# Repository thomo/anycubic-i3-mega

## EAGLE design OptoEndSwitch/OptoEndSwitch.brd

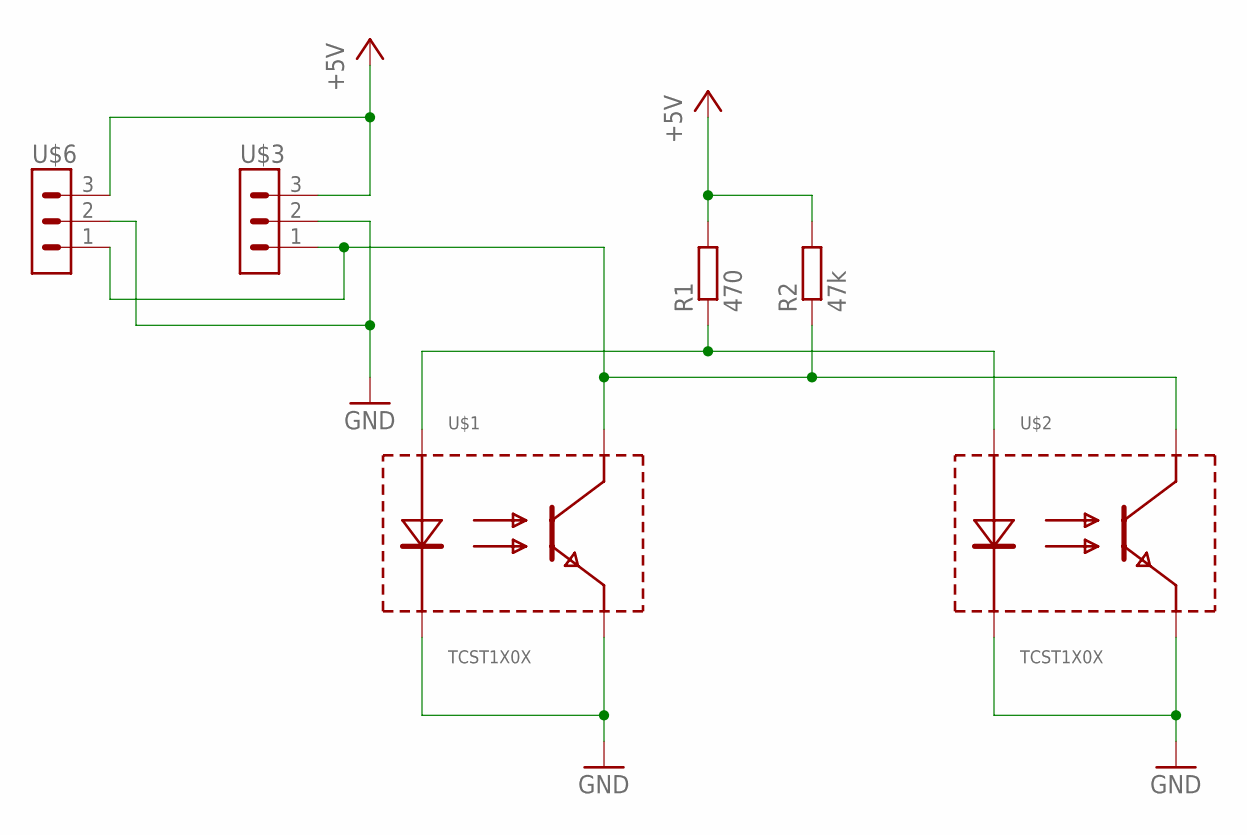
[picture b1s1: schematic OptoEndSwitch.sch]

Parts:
R1: 470; 0207/10
R2: 47k; 0207/10
U$1, U$2: TCST1X0X
U$3, U$6: JST-3PSIDE-SHORT; XH-A-1-SIDE-3P

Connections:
+5V: R1.2, R2.2, U$3.3, U$6.3
GND: U$1.D, U$1.E, U$2.D, U$2.E, U$3.2, U$6.2
unnamed: R2.1, U$1.D+, U$2.D+, U$3.1, U$6.1
unnamed: R1.1, U$1.E+, U$2.E+

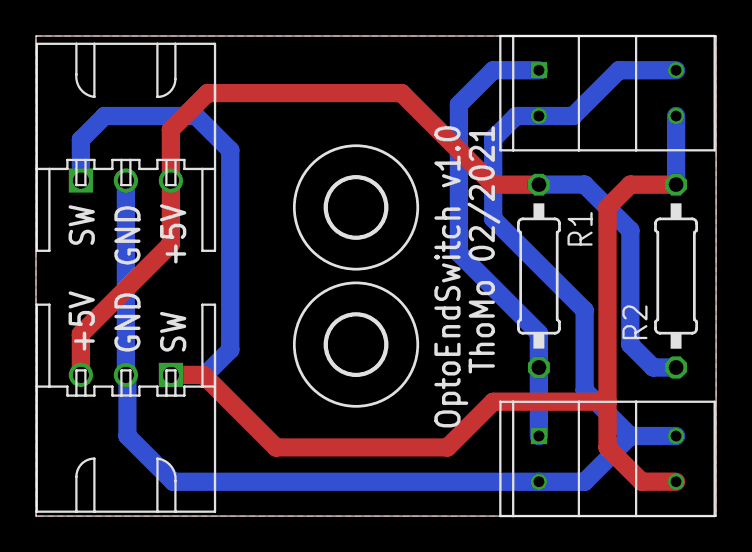
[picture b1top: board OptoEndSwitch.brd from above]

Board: 2 copper layers, 37.8 x 26.7 mm, 8 parts (0 on the bottom side), 4 nets.

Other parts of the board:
U$4, U$5: 3,2

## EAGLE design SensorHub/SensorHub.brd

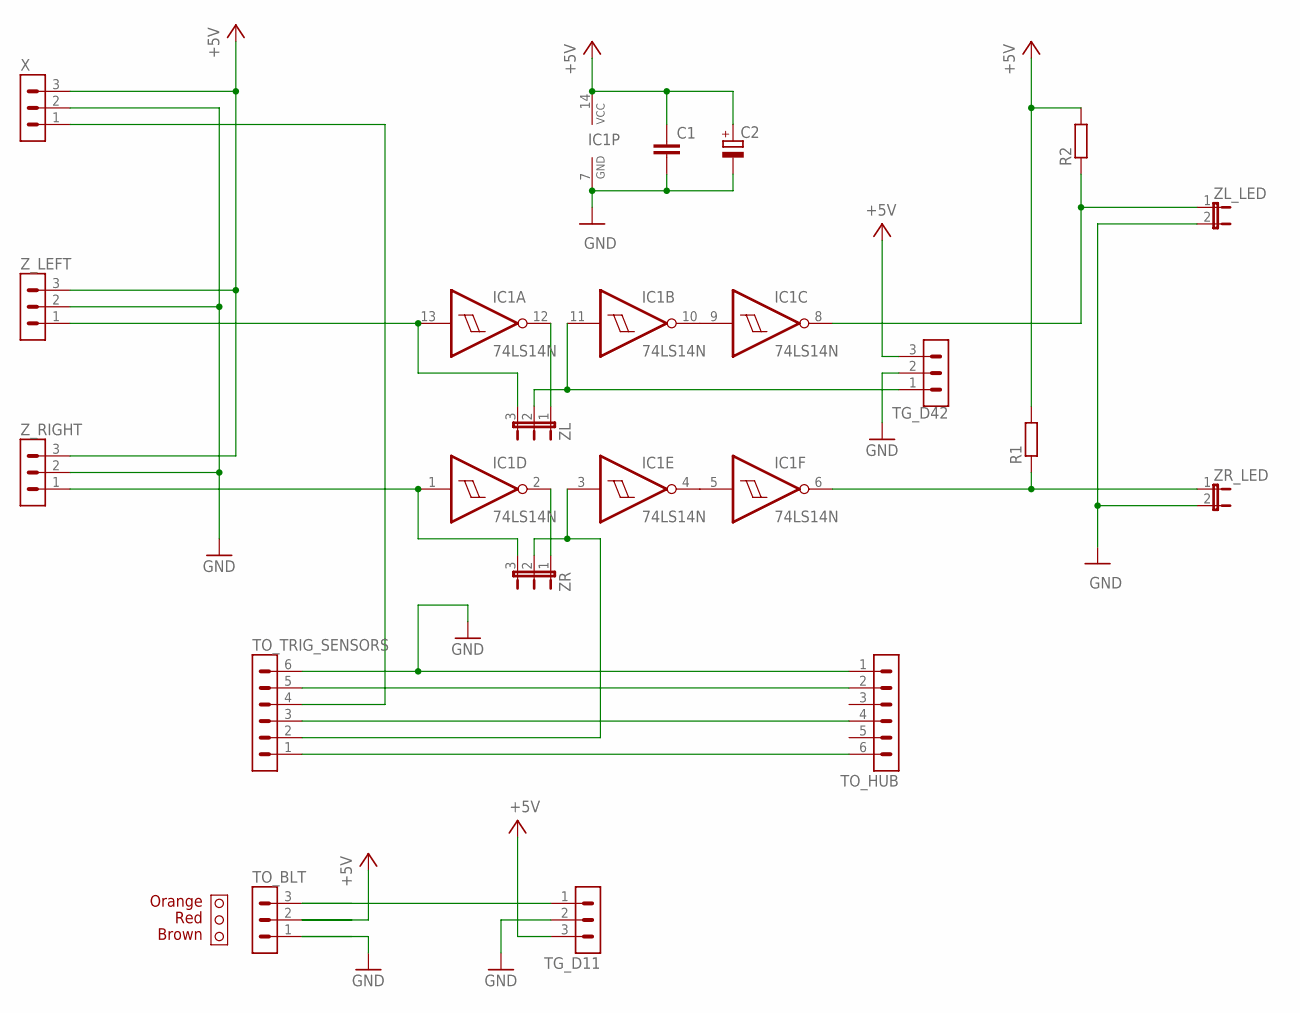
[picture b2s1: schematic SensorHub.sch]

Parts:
C1: C-EU050-030X075; C050-030X075
C2: CPOL-EUE3.5-8; E3,5-8
IC1: 74LS14N; DIL14
R1, R2: R-EU_0207/10; 0207/10
TG_D11, TG_D42: JST-3PTOP; XH-A-TOP-3P
TO_BLT: JST-3PTOP; XH-A-TOP-3P
TO_HUB: JST-6PPH-TOP; PH-TOP-6P
TO_TRIG_SENSORS: JST-6PPH-TOP; PH-TOP-6P
X: JST-3PTOP; XH-A-TOP-3P
ZL: JP2E; JP2
ZL_LED: ZL LED; JP1
ZR: JP2E; JP2
ZR_LED: ZR LED; JP1
Z_LEFT: JST-3PTOP; XH-A-TOP-3P
Z_RIGHT: JST-3PTOP; XH-A-TOP-3P

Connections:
+5V: C1.1, C2.+, IC1.14 (VCC), R1.2, R2.2, TG_D11.3, TG_D42.3, TO_BLT.2, X.3, Z_LEFT.3, Z_RIGHT.3
GND: C1.2, C2.-, IC1.7 (GND), TG_D11.2, TG_D42.2, TO_BLT.1, TO_HUB.1, TO_TRIG_SENSORS.6, X.2, ZL_LED.2, ZR_LED.2, Z_LEFT.2, Z_RIGHT.2
unnamed: IC1.6 (O), R1.1, ZR_LED.1
unnamed: IC1.13 (I), ZL.3, Z_LEFT.1
unnamed: IC1.1 (I), ZR.3, Z_RIGHT.1
unnamed: TO_HUB.4, TO_TRIG_SENSORS.3
unnamed: TO_HUB.2, TO_TRIG_SENSORS.5
unnamed: IC1.11 (I), TG_D42.1, ZL.2
unnamed: TO_HUB.6, TO_TRIG_SENSORS.1
unnamed: IC1.9 (I), IC1.10 (O)
unnamed: TO_TRIG_SENSORS.4, X.1
unnamed: IC1.4 (O), IC1.5 (I)
unnamed: IC1.12 (O), ZL.1
unnamed: TG_D11.1, TO_BLT.3
unnamed: IC1.2 (O), ZR.1
unnamed: IC1.3 (I), TO_TRIG_SENSORS.2, ZR.2
TG_D42: IC1.8 (O), R2.1, ZL_LED.1

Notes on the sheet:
Orange
Red
Brown

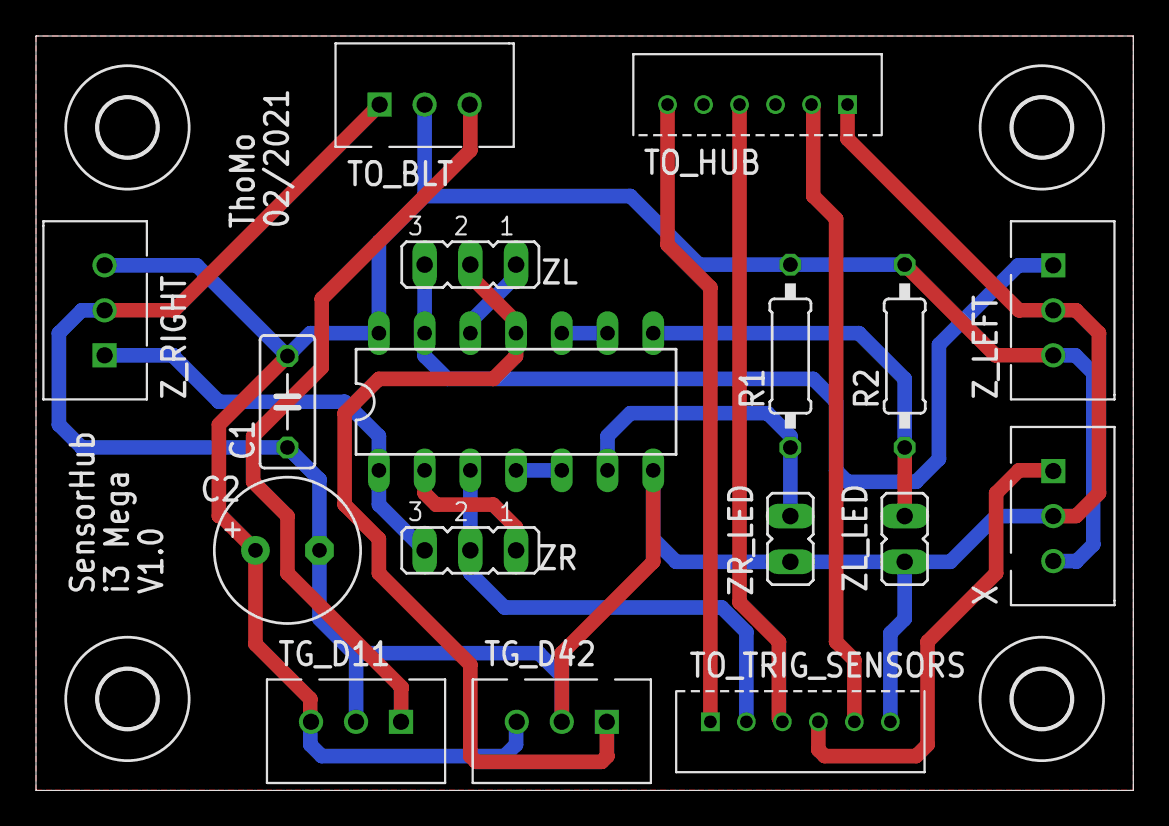
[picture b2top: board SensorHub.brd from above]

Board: 2 copper layers, 61.0 x 41.9 mm, 21 parts (0 on the bottom side), 17 nets.

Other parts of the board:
U$1, U$2, U$3, U$4: 3,2

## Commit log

2021-03-07 init

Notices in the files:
parts and their libraries:
SparkFun-Aesthetics: Licensing: Creative Commons ShareAlike 4.0 International - https://creativecommons.org/licenses/by-sa/4.0
